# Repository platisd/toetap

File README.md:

# ToeTap
A human interface device for your toes 🦶⌨️

## What is ToeTap?

ToeTap is a minimalist USB keyboard and mouse that you control by tapping your toes.
It's designed to be used as a foot pedal for gamers, video makers and editors or anyone who wants to keep their hands free while working in front of a computer.
I use it to scroll through my script while recording videos because I hate moving my hand away just to scroll. It shows a bit on the video and it's annoying.
You can easily adjust it to perform any keyboard or mouse action you want. With up to 3 inputs and no moving parts, it's a simple and reliable tool that you can use to improve your workflow.

Compared to commercial foot pedals, ToeTap is probably slightly cheaper if you know how to solder and can program an Arduino. It's also infinitely more customizable since, you know, it's open source. 🍹

## How does it work?

ToeTap is made of some hardware that involve various components, custom made PCBs and a 3D printed case. It's controlled by an Arduino Pro Micro clone, which is a small board that can act as a USB keyboard or mouse. The ATmega32U4 microcontroller by Microchip is connected to 3 photoresistors that are used to detect when you tap/step on them.

### Hardware

The following components are necessary to build ToeTap:
- 3x [ToeTap PCBs](https://www.pcbway.com/project/shareproject/ToeTap_USB_Controller_7fb3b714.html)
- Arduino Pro Micro clone in a "square" form factor where the USB port is part of the board
  - It is often marketed as `Mini SS Micro ATMEGA32U4`
  - You may need to add some electrical tape on the USB side to make sure it doesn't wiggle when you connect it
- 9x 220Ω resistors
- [3D-printed components](https://www.tinkercad.com/things/i6qfPpNWuRz-toetap)

#### PCB Assembly

To build a fully-fledged ToeTap you will need to solder 3 of the ToeTap PCBs together. The PCBs are designed to be soldered together side by side, with the photoresistors on the top side and everything else on the bottom side. The photoresistors are used to detect when you tap on the ToeTap. The bottom side of the PCBs is where the microcontroller and the resistors are soldered.
Additionally, on the bottom side of the two "side" PCBs, you need to solder the "pad" facing towards the middle PCB. By soldering the PCBs together AND the corresponding pads, you will be able to get all the PCBs to work together as a single unit. The pads of the middle PCB should be left unsoldered.
If you need more detailed instructions, open an issue and I'll be happy to help you out.

### Software

The software is written in C++ and is designed to be compiled with the Arduino IDE.
Some basic filtering is applied to the photoresistor readings to detect when you tap on the ToeTap. The readings are then used to trigger a keyboard or mouse action. The software is designed to be easily customizable, so you can change the keybindings and the sensitivity of the ToeTap to suit your needs.

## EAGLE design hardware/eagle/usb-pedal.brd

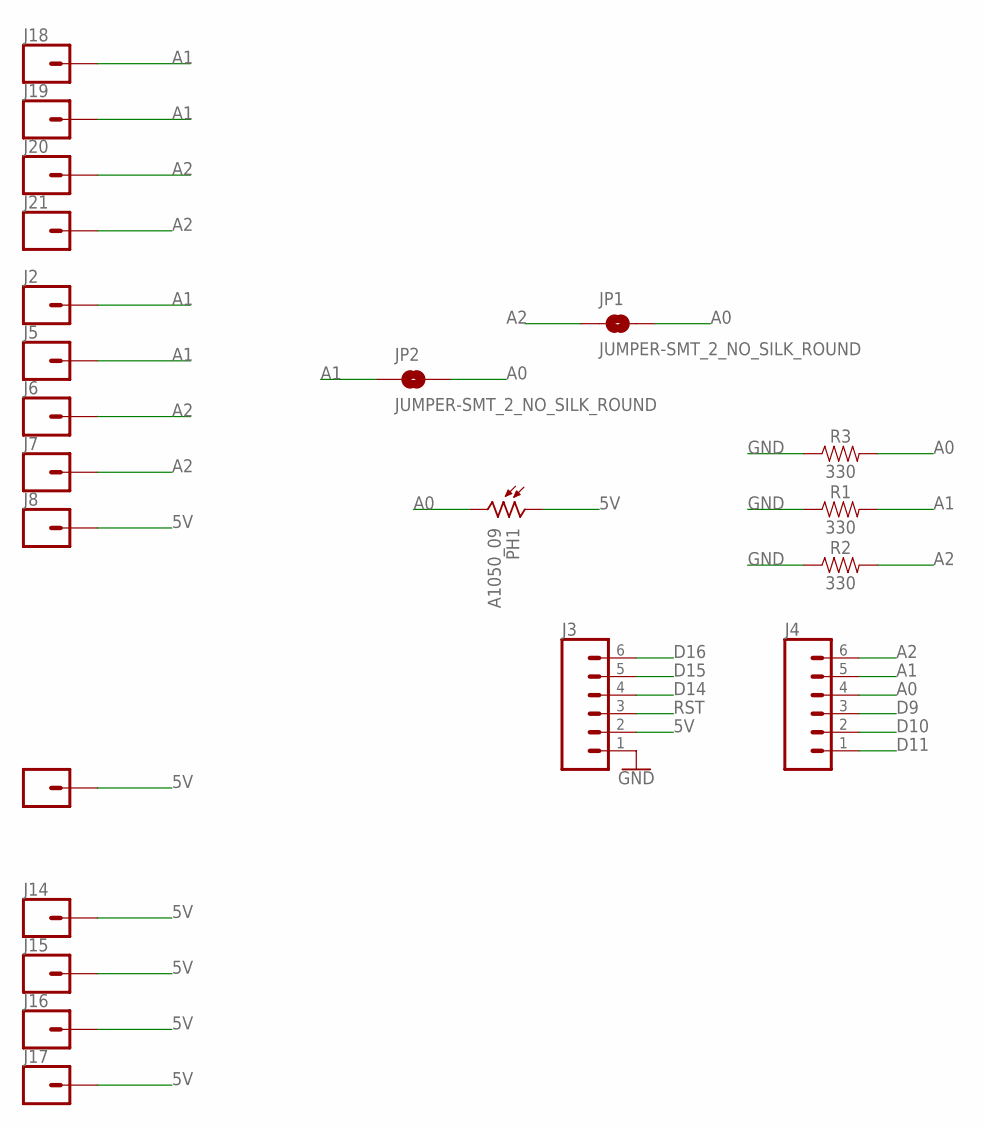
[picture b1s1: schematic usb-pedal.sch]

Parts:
J2, J5, J6, J7, J8, J12, J14, J15, J16, J17, J18, J19, J20, J21: CONN_01SMTSO-256-ET-0.165DIA; SMTSO-256-ET-0.165DIA
J3, J4: CONN_06LOCK; 1X06_LOCK
JP1, JP2: JUMPER-SMT_2_NO_SILK_ROUND; SMT-JUMPER_2_NO_SILK_ROUND
PH1: A1050_09; T0-46-A10XX
R1, R2, R3: 330; AXIAL-0.3

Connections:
5V: J3.2, J8.P$1, J12.P$1, J14.P$1, J15.P$1, J16.P$1, J17.P$1, PH1.1
A0: J4.4, JP1.2, JP2.2, PH1.2, R3.P$2 (2)
A1: J2.P$1, J4.5, J5.P$1, J18.P$1, J19.P$1, JP2.1, R1.P$2 (2)
A2: J4.6, J6.P$1, J7.P$1, J20.P$1, J21.P$1, JP1.1, R2.P$2 (2)
D9: J4.3
D10: J4.2
D11: J4.1
D14: J3.4
D15: J3.5
D16: J3.6
GND: J3.1, R1.P$1 (1), R2.P$1 (1), R3.P$1 (1)
RST: J3.3

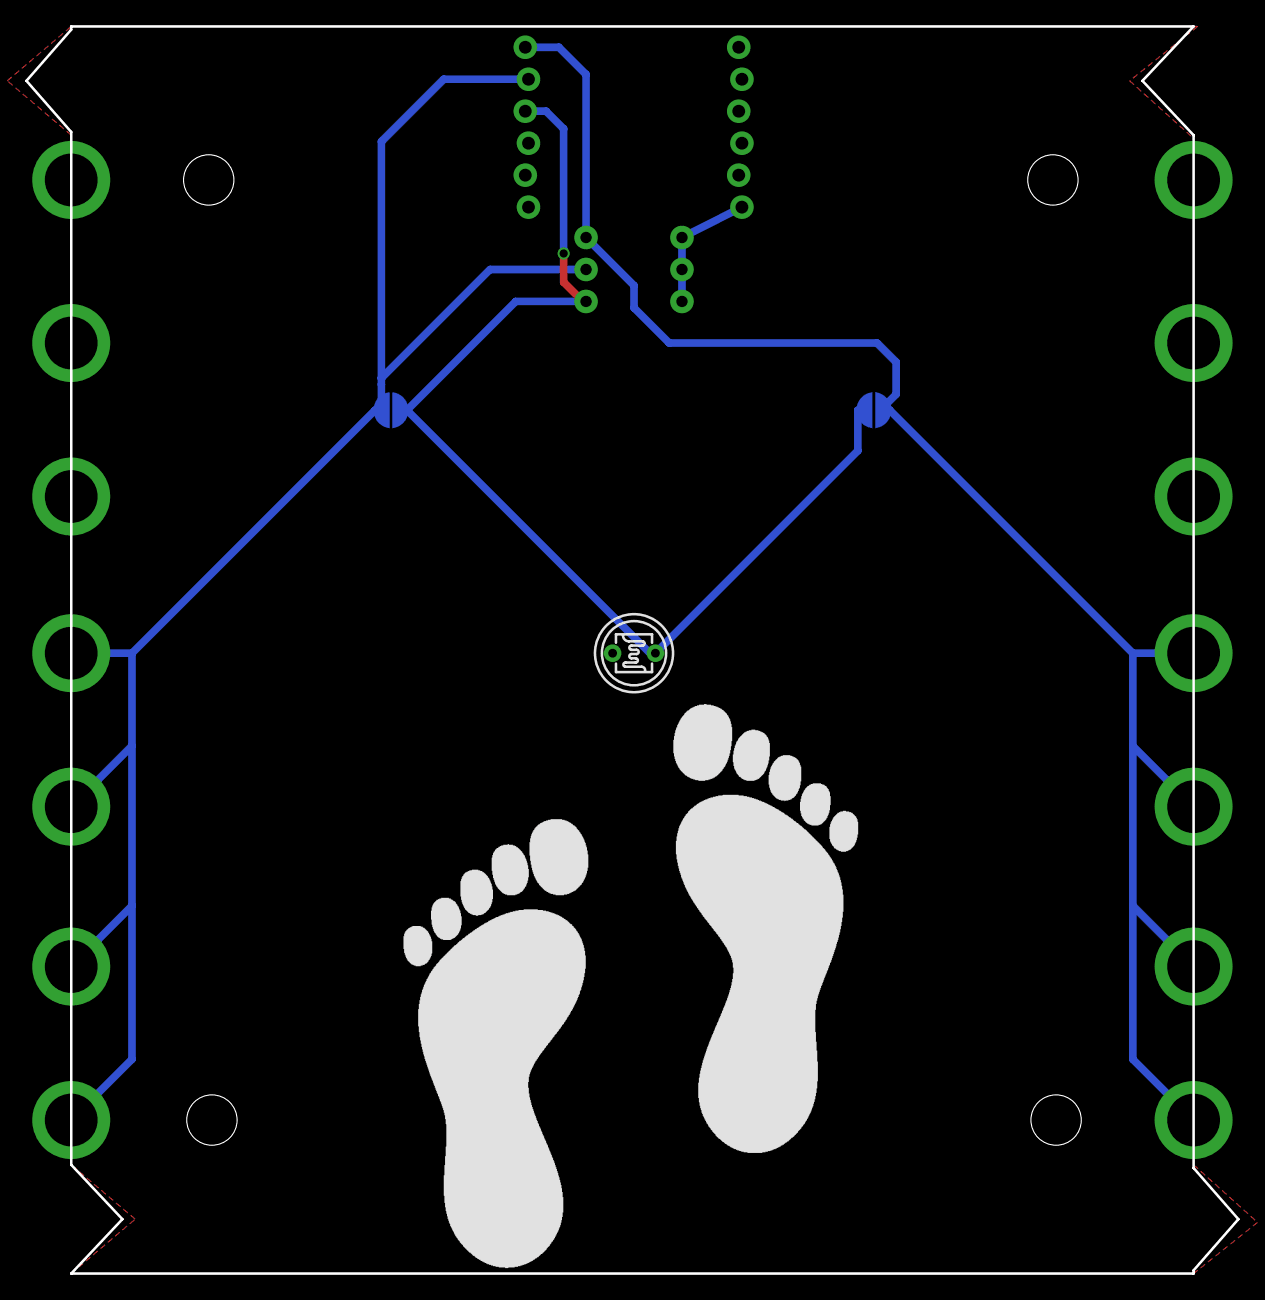
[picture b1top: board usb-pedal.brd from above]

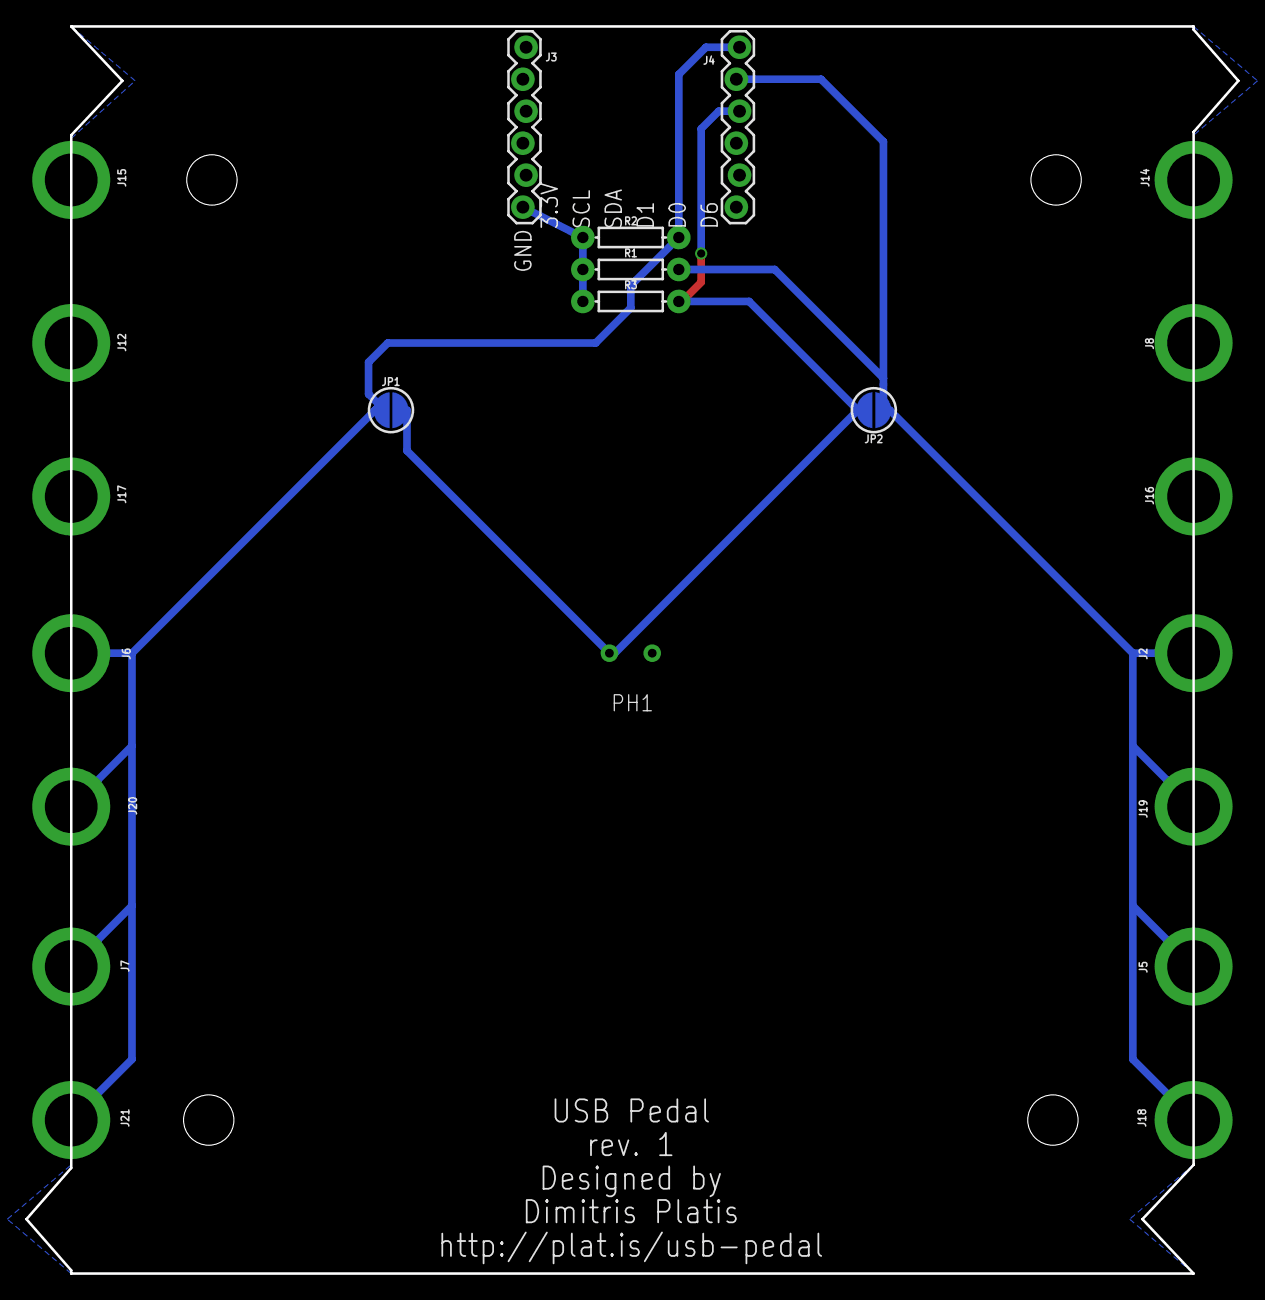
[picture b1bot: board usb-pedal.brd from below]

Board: 2 copper layers, 96.3 x 99.1 mm, 22 parts (7 on the bottom side), 5 nets.

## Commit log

2024-03-16 Add rev.0 hardware schematics
    Errata: The microcontroller board needs to be placed
    'upside-down', i.e. not as implied by the silkscreen
    on the bottom layer of the board.
    If in doubt, get in touch and we can verify the placement
    together.
    The next revision will address this issue. Comitting this
2024-03-16 Add rev.1 board
    Rev.1 solves the slight inconsistency of rev.0's microcontroller
    board placement.
    Now the board should be placed 'as you see it' while in the previous
    version the silkscreen didn't actually match the correct board placement.
2024-03-16 Add arduino sketch
    The sketch detects (after some basic filtering) when it receives no light,
    or in other words is being stepped on, and scrolls the mouse.
    The sketch can be adjusted for any other action supported by the Keyboard and Mouse libraries.
2024-03-17 Add README and images
2024-03-18 Scroll down with the right leg/sensor
2024-03-18 Update main title
2024-03-21 Fix the number of resistors
    We need 3 resistors per board, so 9 in total

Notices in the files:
parts and their libraries:
SparkFun-Connectors: Licensing: Creative Commons ShareAlike 4.0 International - https://creativecommons.org/licenses/by-sa/4.0
